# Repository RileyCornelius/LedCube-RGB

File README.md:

# LedCube
RGB Led Cube controlled by FastLED

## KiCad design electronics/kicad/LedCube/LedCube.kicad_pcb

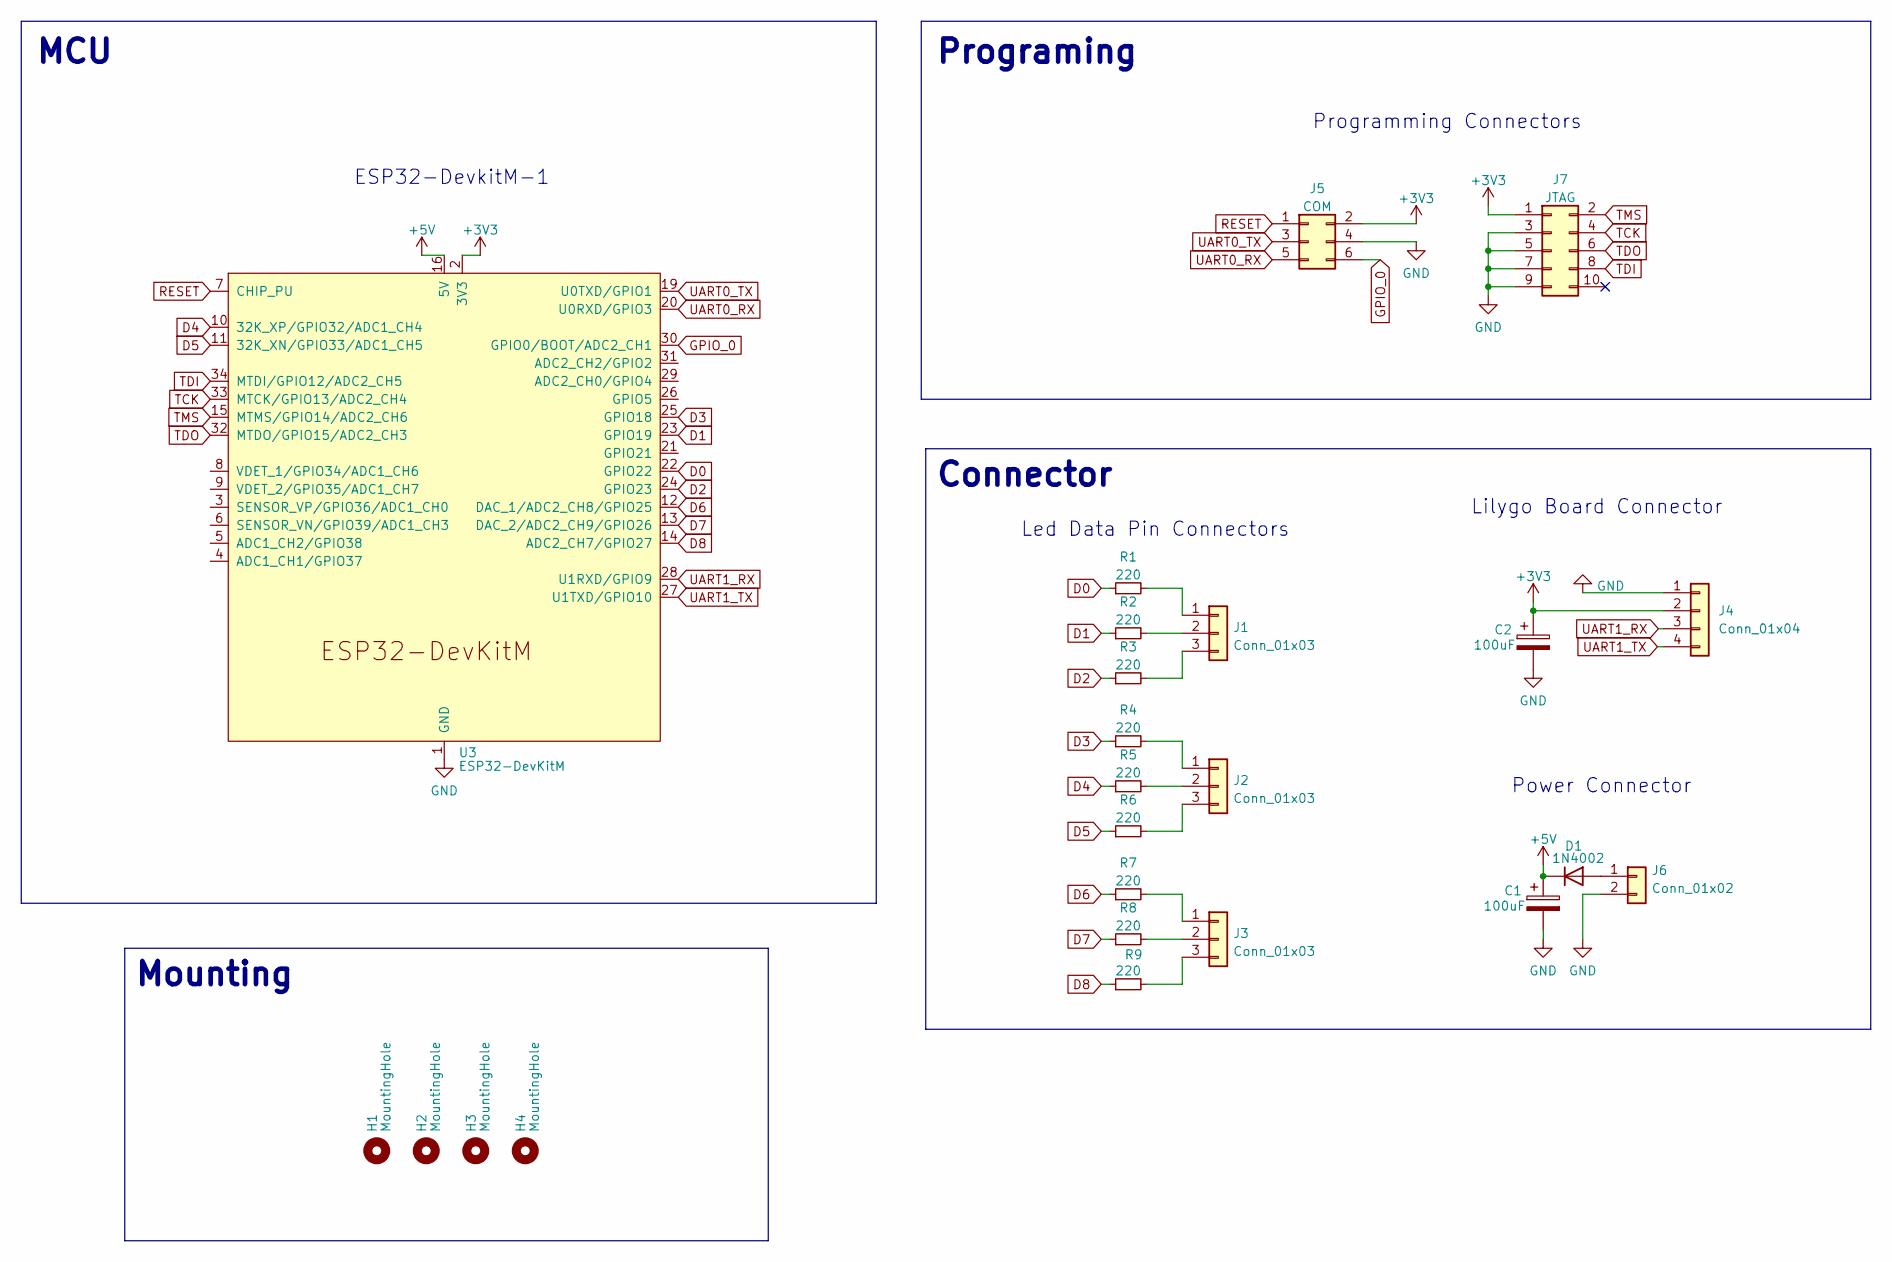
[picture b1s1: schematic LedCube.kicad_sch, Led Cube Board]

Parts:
C1, C2: 100uF; C_Radial_D5.0mm_H5.0mm_P2.00mm
D1: 1N4002; D_DO-15_P10.16mm_Horizontal
H1, H2, H3, H4: MountingHole; MountingHole_3.2mm_M3_Pad
J1, J2, J3: Conn_01x03; JST_XH_B3B-XH-A_1x03_P2.50mm_Vertical
J4: Conn_01x04; Grove_1x04
J5: COM; ESP_PROG_COM; Manufacturer Part Number 20021511-00006T4LF; Digikey Part Number 20021511-00006T4LF-ND
J6: Conn_01x02; JST_XH_B2B-XH-A_1x02_P2.50mm_Vertical
J7: JTAG; ESP_PROG_JTAG; Manufacturer Part Number 3220-10-0100-00; Digikey Part Number 1175-1627-ND
R1, R2, R3, R4, R5, R6, R7, R8, R9: 220; R_0603_1608Metric_Pad0.98x0.95mm_HandSolder
U3: ESP32-DevKitM

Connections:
+3V3: C2.1, J4.2, J5.2, J7.1, U3.2 (3V3)
+5V: C1.1, D1.1 (K), U3.16 (5V)
D0: R1.1, U3.22 (GPIO22)
D1: R2.1, U3.23 (GPIO19)
D2: R3.1, U3.24 (GPIO23)
D3: R4.1, U3.25 (GPIO18)
D4: R5.1, U3.10 (32K_XP/GPIO32/ADC1_CH4)
D5: R6.1, U3.11 (32K_XN/GPIO33/ADC1_CH5)
D6: R7.1, U3.12 (DAC_1/ADC2_CH8/GPIO25)
D7: R8.1, U3.13 (DAC_2/ADC2_CH9/GPIO26)
D8: R9.1, U3.14 (ADC2_CH7/GPIO27)
GND: C1.2, C2.2, J4.1, J5.4, J6.2, J7.3, J7.5, J7.7, J7.9, U3.1 (GND), U3.17 (GND), U3.18 (GND)
GPIO_0: J5.6, U3.30 (GPIO0/BOOT/ADC2_CH1)
unnamed: D1.2 (A), J6.1
unnamed: J1.1, R1.2
unnamed: J1.2, R2.2
unnamed: J1.3, R3.2
unnamed: J2.1, R4.2
unnamed: J2.2, R5.2
unnamed: J2.3, R6.2
unnamed: J3.1, R7.2
unnamed: J3.2, R8.2
unnamed: J3.3, R9.2
RESET: J5.1, U3.7 (CHIP_PU)
TCK: J7.4, U3.33 (MTCK/GPIO13/ADC2_CH4)
TDI: J7.8, U3.34 (MTDI/GPIO12/ADC2_CH5)
TDO: J7.6, U3.32 (MTDO/GPIO15/ADC2_CH3)
TMS: J7.2, U3.15 (MTMS/GPIO14/ADC2_CH6)
UART0_RX: J5.5, U3.20 (U0RXD/GPIO3)
UART0_TX: J5.3, U3.19 (U0TXD/GPIO1)
UART1_RX: J4.3, U3.28 (U1RXD/GPIO9)
UART1_TX: J4.4, U3.27 (U1TXD/GPIO10)

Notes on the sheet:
ESP32-DevkitM-1
Programming Connectors
Programing
MCU
Connector
Mounting
Lilygo Board Connector
Power Connector
Led Data Pin Connectors

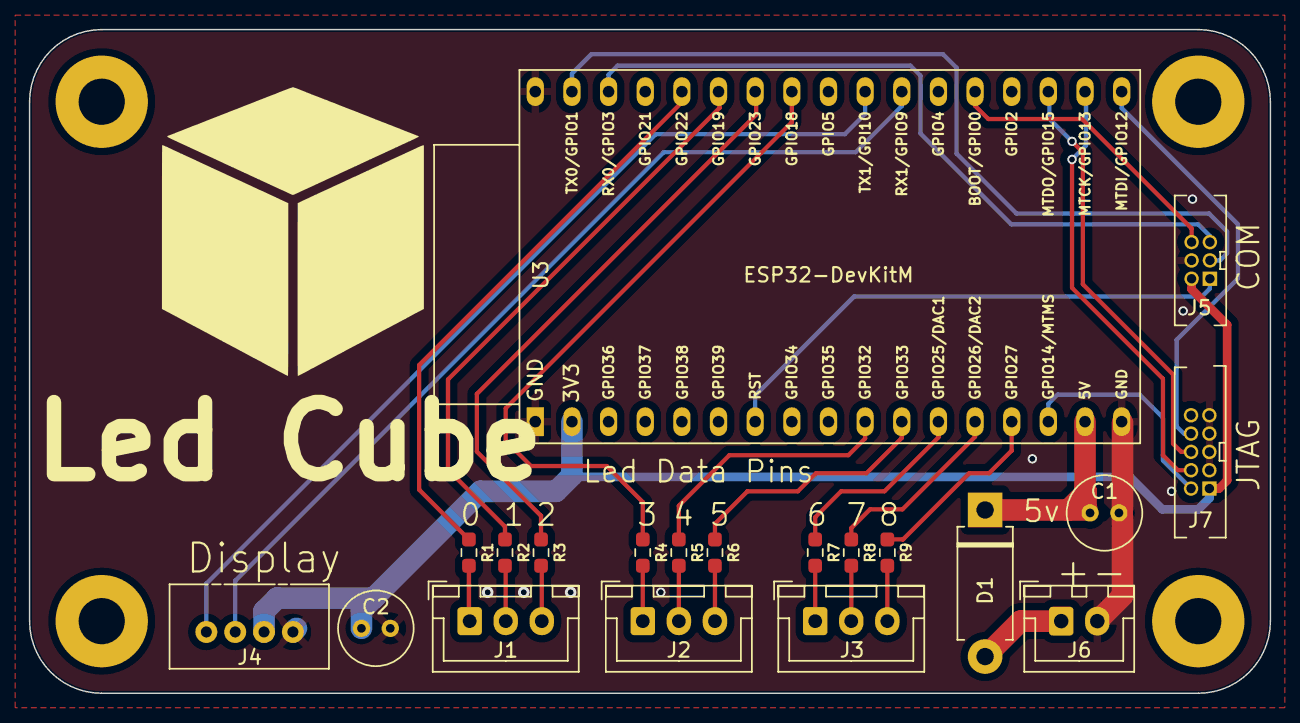
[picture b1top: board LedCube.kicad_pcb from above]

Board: 2 copper layers, 86.0 x 46.0 mm, 24 parts (0 on the bottom side), 32 nets.

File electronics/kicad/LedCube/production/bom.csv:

Designator,Footprint,Quantity,Value,LCSC Part #
"C1, C2",C_Radial_D5.0mm_H5.0mm_P2.00mm,2,100uF,
D1,D_DO-15_P10.16mm_Horizontal,1,D,
"H1, H2, H3, H4",MountingHole_3.2mm_M3_Pad,4,MountingHole,
"J1, J2, J3",JST_XH_B3B-XH-A_1x03_P2.50mm_Vertical,3,Conn_01x03,
J4,Grove_1x04,1,Conn_01x04,
J5,ESP_PROG_COM,1,COM,
J6,JST_XH_B2B-XH-A_1x02_P2.50mm_Vertical,1,Conn_01x02,
J7,ESP_PROG_JTAG,1,JTAG,
"R1, R2, R3, R4, R5, R6, R7, R8, R9",0603,9,220,
U3,ESP32-DevKitM,1,ESP32-DevKitM,

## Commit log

2022-09-23 Init
2022-09-23 Add firmware
2022-12-03 Add IO and Timer utlis
2022-12-05 Update Button, Timer, Animation and Cube
2022-12-10 Add state machine to Animator class
2022-12-12 Refactor Debounce class
2022-12-15 Add I2S parallel data transfer
2022-12-23 Add Logger.h
2022-12-23 Clean up code
2022-12-23 Add benchmark begin and end defines to Timer
2022-12-23 Add beginning and ending virtual functions to Animation class
2022-12-23 Update Animator to no longer use a pointer array instead of a linked list
2022-12-23 Update Cube class to support serpent led layout
2022-12-23 Add pause function to Animator class
2022-12-24 Add Logger class
2022-12-28 Readd state machine to Animator class with virtual beginning and ending functions
2022-12-29 Add line, sphere and shell functions to Cube class
2023-01-14 Fix serpentine layout algorithm
2023-01-15 Add more animations
2023-03-17 Rename firmware project
2023-03-17 Add tower test firmware
2023-03-17 Add mechanical accessory files
2023-03-17 Add mechanical case files
2023-03-17 Add electronics related files
2023-03-19 Update tower test with multiple data lines
2023-03-24 Add mounting holes to the case
2023-03-31 Rename TowerTest firmware
2023-03-31 Add T-Display-S3 driver project
2023-03-31 Add T-Embed driver project
2023-03-31 Add SquareLine project source files
2023-03-31 Add generated lvgl c files to T-Display-S3
2023-03-31 Add generated lvgl c files to T-Embed
2023-04-03 Add connectors to KiCad schematic
2023-04-04 Add full case part
2023-04-05 Add screen mount to case
2023-04-10 Add power cut out
2023-04-15 Add power supply mounting brackets and fan cut out
2023-04-15 Update kicad schematic
2023-04-16 Add simple message system between display and cube using uart
2023-04-19 Add esp32 devkit footprint
2023-04-19 Create ESP32-DevkitM-1 footprint
2023-04-20 Finish KiCad PCB board
2023-04-21 Generate PCB step file
2023-04-22 Finish mechanical case design
2023-04-22 Generate case stl
2023-04-22 Add over the air updates to LedCube firmware
2023-04-22 Remove unneeded file from T-Embed libs
2023-04-22 Remove T-Display firmware
2023-04-22 Move Square Line source
2023-04-22 Refactor lv_setup
2023-04-22 Add over the air updates to T-Embed firmware
2023-04-23 Update led pin defines
2023-04-28 Update kicad gerbers
2023-04-28 Add basic over the air update ui
2023-04-30 Add AnimatorState
2023-04-30 Add Logger
2023-04-30 Move OTA to its own folder
2023-04-30 Fix play button display sync
2023-04-30 Add Logger to T-Embed
2023-04-30 Add Display functions to LedCube
2023-04-30 Update Animator with display macros
2023-04-30 Update OTA with logging and display functions
2023-04-30 Rename pin_config to config
2023-04-30 Add display functions to T-Embed
2023-04-30 Update OTA with logger
2023-04-30 Update ui_events with display and logging functions on T-Embed
2023-04-30 Remove un needed folder from libs
2023-04-30 Move ota and cube com files into folders on T-Embed
2023-05-06 Replaced Button with SimpleButton class
2023-05-06 Add include path to compiler build flags
2023-05-06 Fix flipped vcc and gnd in KiCad
2023-05-06 Refactor function names
2023-05-07 Rename stop() to clear()
2023-05-07 Fix getIndex
2023-05-07 Fix OTA comms
2023-05-07 Add Ripple animation
2023-05-11 Fix message enum string conversion issues
2023-05-13 Rename cube class
2023-05-20 Disable logger
2023-05-20 Fix display comms parsing
2023-05-20 Add new animations - Spiral, Rainbow, Shell and Sphere
2023-05-20 Remove old test code
2023-05-20 Refactor macro names
2023-05-21 Fix initial led clear
2023-05-21 Add bounce animation
2023-05-21 Add Blynk app support
2023-05-21 Add ascii font function to cube and font based animations
2023-05-21 Add extra fonts
2023-05-22 Remove fonts because they look similar
2023-05-22 Fix ota progress display update
2023-05-22 Use rotary encoder to change animations
2023-05-22 Update square line to 1.3.0 which changes folder structure
2023-05-22 Add rotary encoder page
2023-05-31 Add 3d model pictures
2023-08-19 Add triangle and square functions
2023-08-19 Add Point operator overloads
2023-08-19 Add Rain animation
2023-08-19 Update font animation to take in a string
2023-08-19 Update Ripple with gradient
2023-08-19 Move Point to its own .h file
2023-08-21 Add Sparkles animation
2023-08-22 Add rotate by axis
2023-08-22 Add Vector3 and Quaternion
2023-08-23 Update Vector3 rotate to rotate it self
2023-08-23 Move all math classes into Math3D
2023-08-23 Update Vector3 and Point constructors
2023-08-23 Update Cube to use const refences
2023-08-24 Add TextRotate animation
2023-08-26 Update Vector3 rotate
2023-08-26 Add random functions
2023-08-26 Rename variables and small fixes
2023-08-26 Update Rain animation
2023-08-26 Add FireWorks animation
2023-08-27 Rename setVoxel to setLed
2023-08-27 Add cube and box shapes to Cube class
2023-08-27 Update FireWorks animation
2023-09-04 Add radiate to Cube class
2023-09-04 Add Box animation
2023-09-04 Add smile animation
2023-09-04 Add Arrow animation
2023-09-06 Start Pacman animation
2023-09-06 Add out of bound check to Cube
2023-09-07 Add ghost chasing pacman
2025-02-22 Remove OTA and Blynk
2025-02-22 Refactor file structure
2025-02-22 Clean up Animator
2025-02-22 Add init to Cube
2025-02-22 Fix Animator beginning
2025-02-22 Update from cpp 11 to cpp 17
2025-02-22 Rename LedCube-TowerTest to TowerTest
2025-02-22 Rename T-Embed-LedCube to LedCube-T-Embed-Display
2025-02-22 Start moving animations into their own files
2025-02-22 Move all animations into their own files
